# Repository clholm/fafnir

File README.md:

# fafnir
KiCad project files for the Fafnir Overdrive, a CD4049UBE overdrive (similar to the Greedtone or Red LLama overdrives). V2 adds a Baxandall tone stack that uses one of the CD4049UBE's channels.

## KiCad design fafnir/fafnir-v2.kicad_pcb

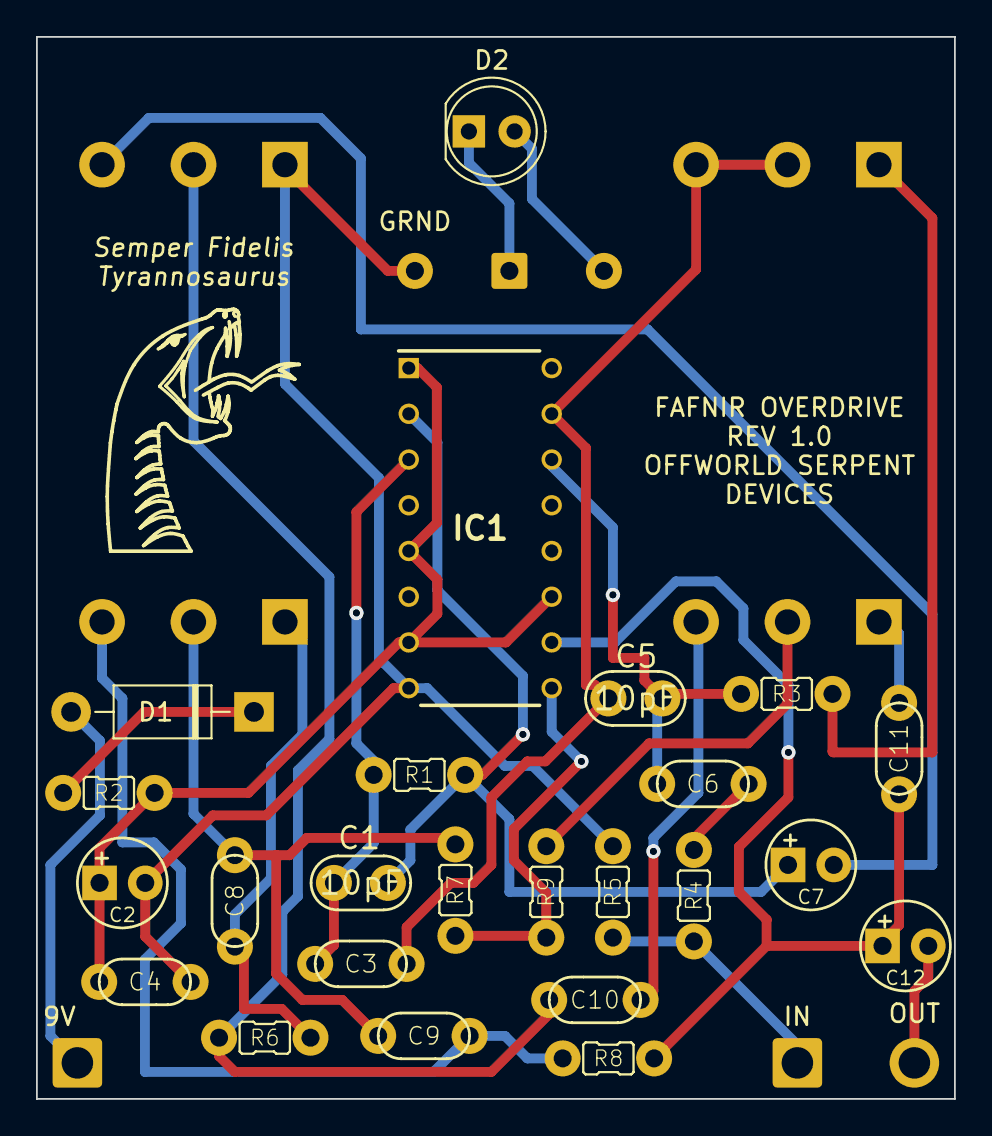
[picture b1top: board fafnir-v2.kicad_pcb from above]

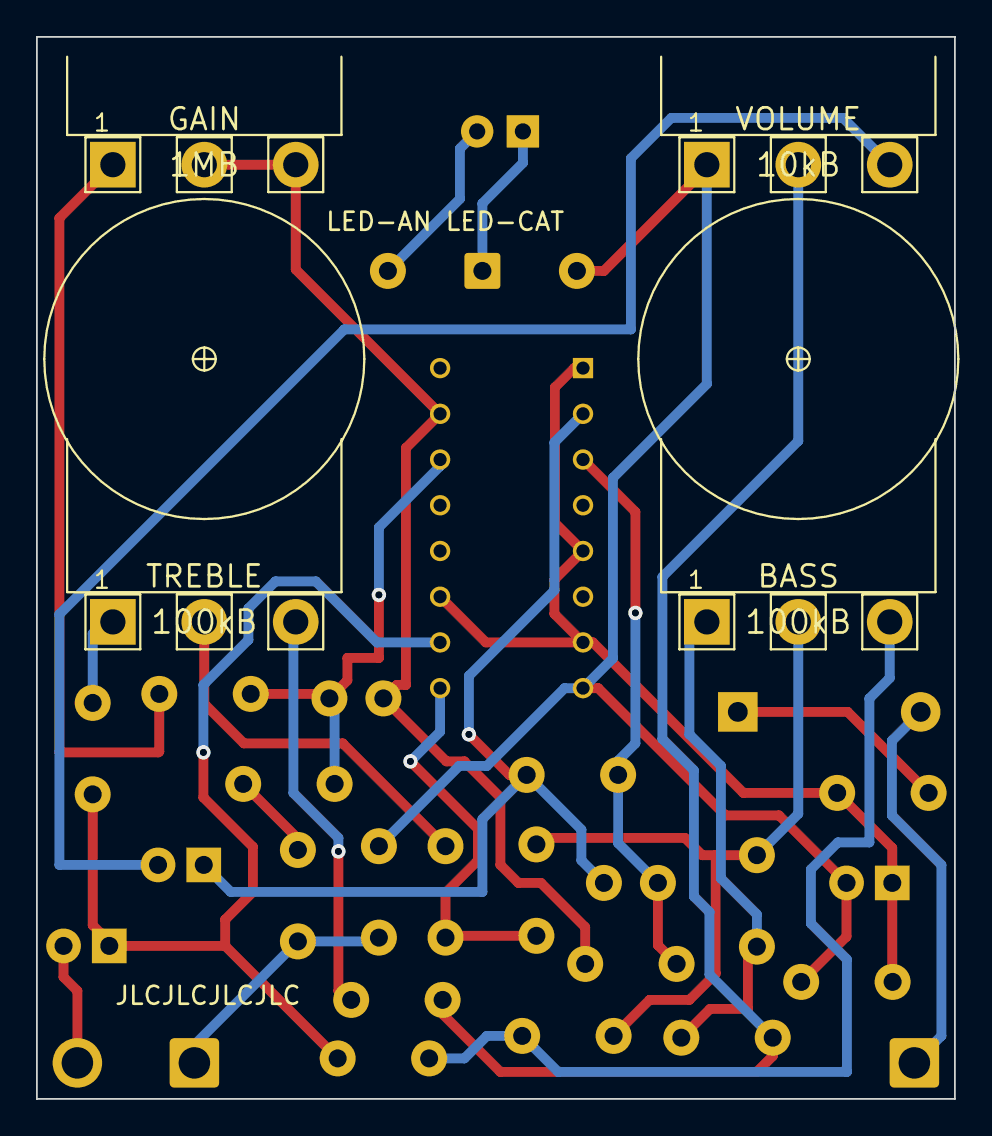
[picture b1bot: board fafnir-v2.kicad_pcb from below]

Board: 2 copper layers, 51.0 x 59.0 mm, 34 parts (6 on the bottom side), 24 nets.

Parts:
9V: SolderWire-1sqmm_1x01_D1.4mm_OD2.7mm
BASS: 100kB; 16MM_T.MOUNT
C1, C5: 10pF; 3mm-diameter-cap
C2: 100uF; 0502
C3, C9: 47nF; 0.2_.SML
C4: .1uF; 0.2_.SML
C6, C8, C11: 22nF; 0.2_.SML
C7: 10uF; 0502
C10: 2.2nF; 0.2_.SML
C12: 4.7uF; 0502
D1: 1N5817; D_DO-41_SOD81_P10.16mm_Horizontal
D2: LED; LED_D5.0mm
GAIN: 1MB; half-pot
GRND: SolderWire-1sqmm_1x01_D1.4mm_OD2.7mm
IC1: CD4049UBE; DIP794W53P254L1930H508Q16N
IN: SolderWire-1sqmm_1x01_D1.4mm_OD2.7mm
LED-AN: SolderWire-1sqmm_1x01_D1.4mm_OD2.7mm
LED-CAT: SolderWire-1sqmm_1x01_D1.4mm_OD2.7mm
OUT: SolderWire-1sqmm_1x01_D1.4mm_OD2.7mm
R1: 10M; 0.2_
R2: 47R; 0.2_
R3, R4: 100k; 0.2_
R5: 1M; 0.2_
R6: 15k; 0.2_
R7: 10k; 0.2_
R8: 12k; 0.2_
R9: 4.7k; 0.2_
TREBLE: 100kB; 16MM_T.MOUNT
VOLUME: 10kB; half-pot

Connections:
+9V: 9V.1, D1.2
Earth: C2.2, C4.2, GRND.1, IC1.8, R5.2, VOLUME.1
INPUT: IN.1, R4.2, R5.1
LED-AN: D2.2, LED-AN.1
LED-CAT: D2.1, LED-CAT.1
unnamed: BASS.1, C8.1, R6.2
unnamed: BASS.2, C8.2, C9.1, R7.2
unnamed: BASS.3, C9.2, R8.2
unnamed: C1.1, C7.1, IC1.2, R1.1
unnamed: C1.2, C3.2, IC1.3, R1.2
unnamed: C3.1, C5.1, GAIN.2, GAIN.3, IC1.15
unnamed: C5.2, C6.2, IC1.14, R3.2
unnamed: C6.1, R4.1
unnamed: C7.2, VOLUME.3
unnamed: C10.1, TREBLE.3
unnamed: C10.2, R6.1, VOLUME.2
unnamed: C11.1, C12.1, IC1.10, R8.1
unnamed: C11.2, TREBLE.1
unnamed: D1.1, R2.2
unnamed: GAIN.1, R3.1
unnamed: IC1.9, R7.1, R9.2
unnamed: R9.1, TREBLE.2
OUTPUT: C12.2, OUT.1
VAA: C2.1, C4.1, IC1.1, IC1.5, IC1.7, IC1.11, R2.1

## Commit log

2020-10-30 annotated schematic v1.0
2020-11-11 v2 schematic, with Baxandall tone stack
2021-03-09 using CD4049UBE for bax
2021-03-09 file cleanup
2021-03-27 moved volume before bax, seems to work better
2021-04-29 update with gerber and drill files, v2 is working
